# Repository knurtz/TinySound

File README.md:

# TinySound
Tiny audio module with SD card reader, STM32 and 3W class-D audio amplifier.

## Parts list

- STM32G030K6 microcontroller
- MAX98360 class-D audio amp with I2S interface
- SD card slot

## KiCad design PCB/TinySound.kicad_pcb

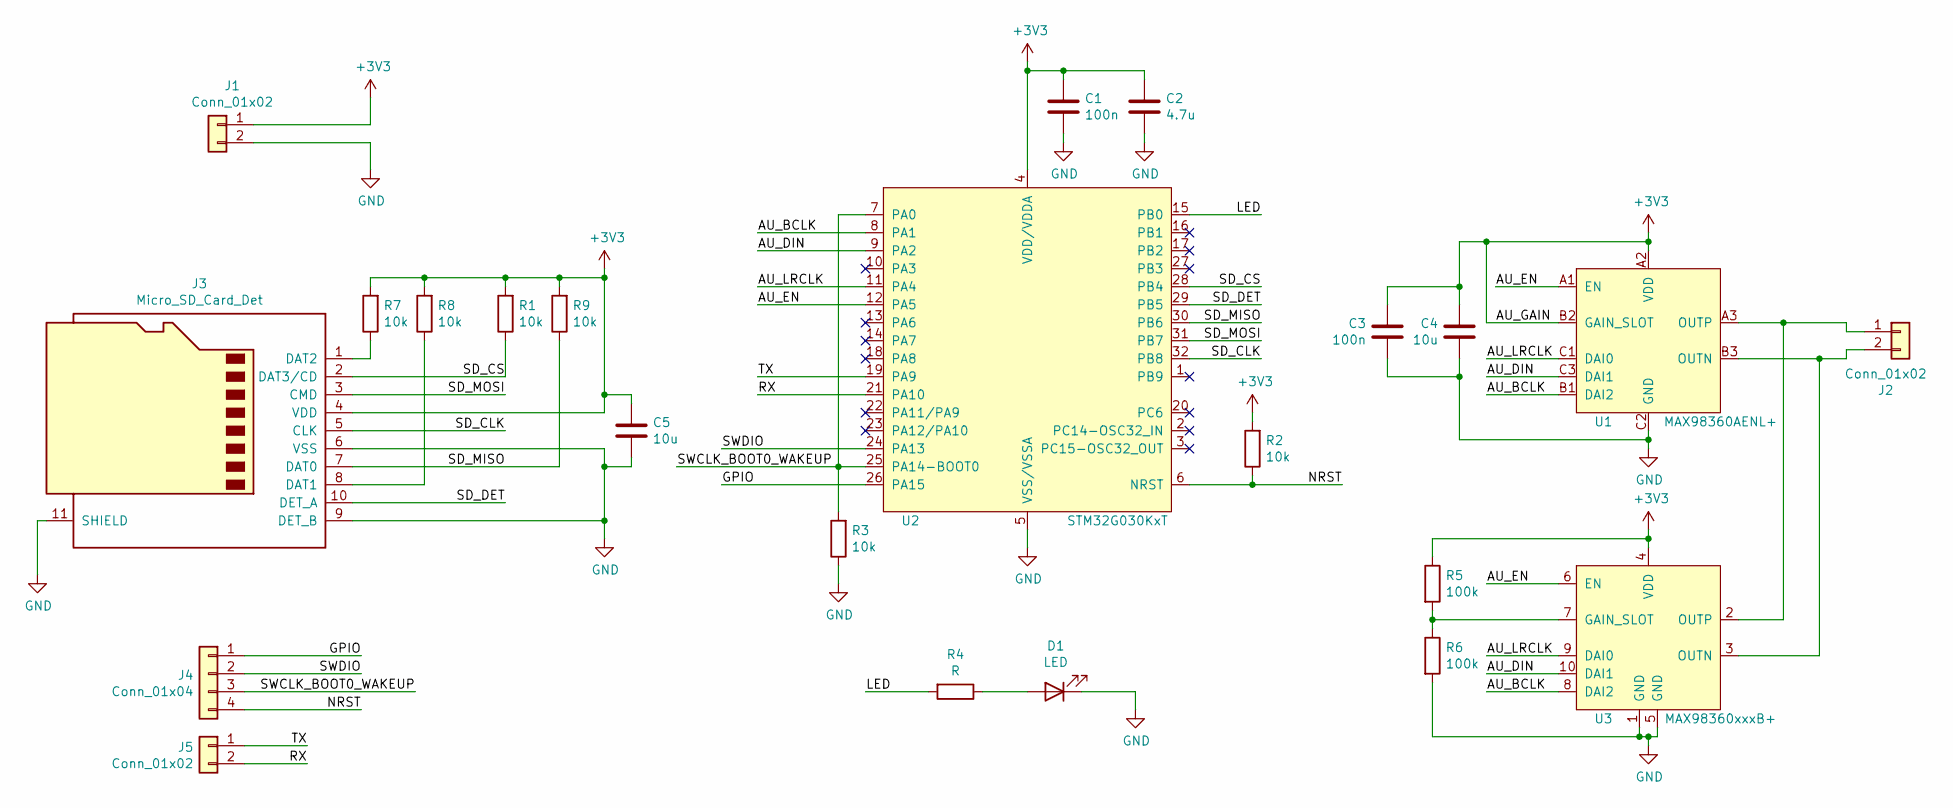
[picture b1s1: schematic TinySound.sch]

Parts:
C1, C3: 100n; C_0603_1608Metric
C2: 4.7u; C_0603_1608Metric
C4, C5: 10u; C_0603_1608Metric
D1: LED; LED_0603_1608Metric
J1, J2, J5: Conn_01x02; PinHeader_1x02_P2.54mm_Vertical
J3: Micro_SD_Card_Det; AMPHENOL_1140084168
J4: Conn_01x04; PinHeader_1x04_P2.54mm_Vertical
R1, R2, R3, R7, R8, R9: 10k; R_0603_1608Metric
R4: R; R_0603_1608Metric
R5, R6: 100k; R_0402_1005Metric
U1: MAX98360AENL+; Maxim_WLP-9_1.595x1.415_Layout3x3_P0.4mm_Ball0.27mm_Pad0.25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; Farnell 3288145
U2: STM32G030KxT; LQFP-32_7x7mm_P0.8mm; Farnell 3246910
U3: MAX98360xxxB+; FC2QFN-10

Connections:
+3V3: C1.1, C2.1, C3.2, C4.2, C5.1, J1.1, J3.4 (VDD), R1.2, R2.2, R5.1, R7.2, R8.2, R9.2, U1.A2 (VDD), U1.B2 (GAIN_SLOT), U2.4 (VDD/VDDA), U3.4 (VDD)
/AU_BCLK: U1.B1 (DAI2), U2.8 (PA1), U3.8 (DAI2)
/AU_DIN: U1.C3 (DAI1), U2.9 (PA2), U3.10 (DAI1)
/AU_EN: U1.A1 (EN), U2.12 (PA5), U3.6 (EN)
/AU_LRCLK: U1.C1 (DAI0), U2.11 (PA4), U3.9 (DAI0)
/GPIO: J4.1, U2.26 (PA15)
/LED: R4.2, U2.15 (PB0)
/NRST: J4.4, R2.1, U2.6 (NRST)
/RX: J5.2, U2.21 (PA10)
/SD_CLK: J3.5 (CLK), U2.32 (PB8)
/SD_CS: J3.2 (DAT3/CD), R1.1, U2.28 (PB4)
/SD_DET: J3.10 (DET_A), U2.29 (PB5)
/SD_MISO: J3.7 (DAT0), R9.1, U2.30 (PB6)
/SD_MOSI: J3.3 (CMD), U2.31 (PB7)
/SWCLK_BOOT0_WAKEUP: J4.3, R3.2, U2.7 (PA0), U2.25 (PA14-BOOT0)
/SWDIO: J4.2, U2.24 (PA13)
/TX: J5.1, U2.19 (PA9)
GND: C1.2, C2.2, C3.1, C4.1, C5.2, D1.1 (K), J1.2, J3.6 (VSS), J3.9 (DET_B), J3.11 (SHIELD), R3.1, R6.2, U1.C2 (GND), U2.5 (VSS/VSSA), U3.1 (GND), U3.5 (GND)
unnamed: D1.2 (A), R4.1
unnamed: J2.1, U1.A3 (OUTP), U3.2 (OUTP)
unnamed: J2.2, U1.B3 (OUTN), U3.3 (OUTN)
unnamed: J3.1 (DAT2), R7.1
unnamed: J3.8 (DAT1), R8.1
unnamed: R5.2, R6.1, U3.7 (GAIN_SLOT)

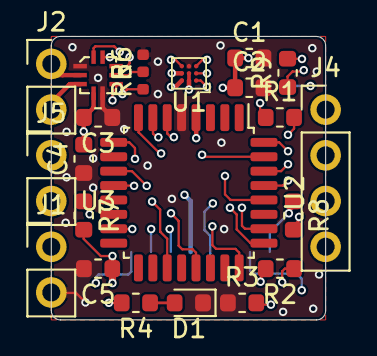
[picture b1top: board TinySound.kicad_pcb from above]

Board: 4 copper layers, 15.2 x 15.7 mm, 23 parts (1 on the bottom side), 24 nets.

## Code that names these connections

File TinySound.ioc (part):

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Mcu.Name=STM32G031K(4-6-8)Tx
Mcu.Package=LQFP32
Mcu.UserName=STM32G031K6Tx
PA0.Mode=SYS_WakeUp0
PA0.Signal=SYS_WKUP1
PA1.Mode=Half_Duplex_Master
PA1.Signal=I2S1_CK
PA10.Mode=Asynchronous
PA10.Signal=USART1_RX
PA13.Mode=Serial_Wire
PA13.Signal=SYS_SWDIO
PA14-BOOT0.Mode=Serial_Wire
PA14-BOOT0.Signal=SYS_SWCLK
PA2.Mode=Half_Duplex_Master
PA2.Signal=I2S1_SD
PA4.Mode=Half_Duplex_Master
PA4.Signal=I2S1_WS
PA5.GPIOParameters=GPIO_Label
PA5.GPIO_Label=AU_EN
PA5.Signal=GPIO_Output
PA9.Mode=Asynchronous
PA9.Signal=USART1_TX
PB0.GPIOParameters=GPIO_Label
PB0.GPIO_Label=LED
PB0.Signal=GPIO_Output
PB4.GPIOParameters=GPIO_Label
PB4.GPIO_Label=SD_CS
PB4.Signal=GPIO_Output
PB5.GPIOParameters=GPIO_Label
PB5.GPIO_Label=SD_DET
PB5.Signal=GPIO_Input
PB6.Mode=Full_Duplex_Master
PB6.Signal=SPI2_MISO
PB7.Mode=Full_Duplex_Master
PB7.Signal=SPI2_MOSI
PB8.Mode=Full_Duplex_Master
PB8.Signal=SPI2_SCK
PF2\ -\ NRST.Mode=Clock-out
PF2\ -\ NRST.Signal=RCC_MCO
RCC.HSE_VALUE=8000000
RCC.SYSCLKFreq_VALUE=32000000
RCC.SYSCLKSource=RCC_SYSCLKSOURCE_PLLCLK
board=custom

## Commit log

2020-12-06 [Inital commit]
2020-12-06 [PCB] Additional resistors for SD card
2020-12-06 [PCB] Fixed wiring error for SWD
2020-12-06 [PCB] Moved resistor and redid the necessary routing!
2020-12-07 [PCB] Minor tweaks
2020-12-07 [PCB] Some adjustments to solder mask for Gerber export
2020-12-08 [PCB] Generated interactive HTML BOM
2020-12-18 Minor change in layout
2021-04-11 [Documents] Datasheet and manual for STM32G031K6
2021-04-11 [Images] of soldering process
2021-04-11 [Code] Copied code from EmergencyWake and stripped down to audio parts only.
2021-04-13 [Code] Some rearrangements of code fragments
2021-04-16 [Code] Added CubeMX project
2021-04-16 [Code] Added SPI FatFS bindings by kiwih
2021-04-16 [Code] Adjusted diskio stuff for project, added SD test command to shell
2021-04-18 [Code] Audio output works thanks to DMMA
2021-04-18 [Code] List files and play 'em
